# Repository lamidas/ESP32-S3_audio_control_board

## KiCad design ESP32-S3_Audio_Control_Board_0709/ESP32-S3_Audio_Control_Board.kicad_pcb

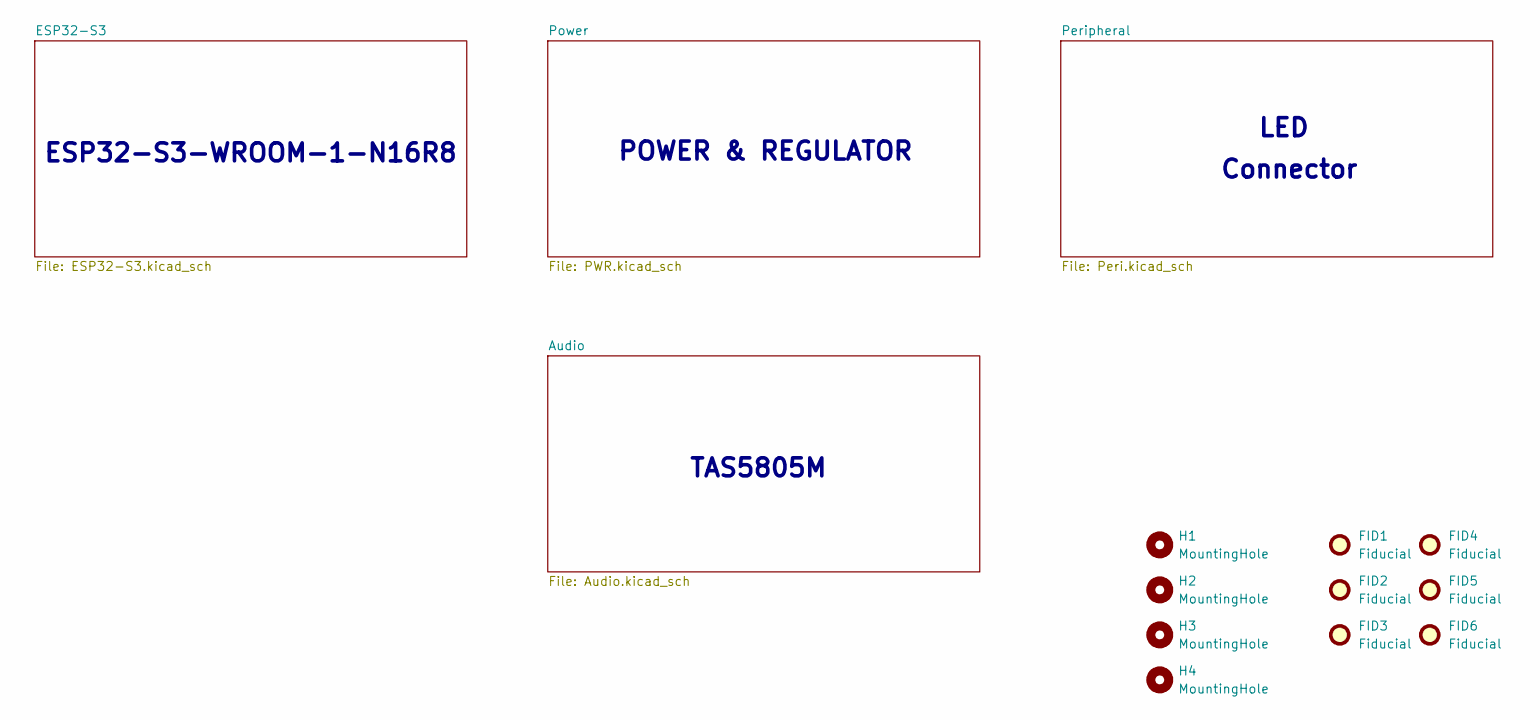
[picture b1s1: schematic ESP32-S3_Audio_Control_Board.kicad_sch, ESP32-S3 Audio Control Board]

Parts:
FID1, FID2, FID3, FID4, FID5, FID6: Fiducial; Fiducial_1mm_Mask2mm
H1, H2, H3, H4: MountingHole; MountingHole_3.5mm

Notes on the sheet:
ESP32-S3-WROOM-1-N16R8
Connector
TAS5805M
LED
POWER & REGULATOR

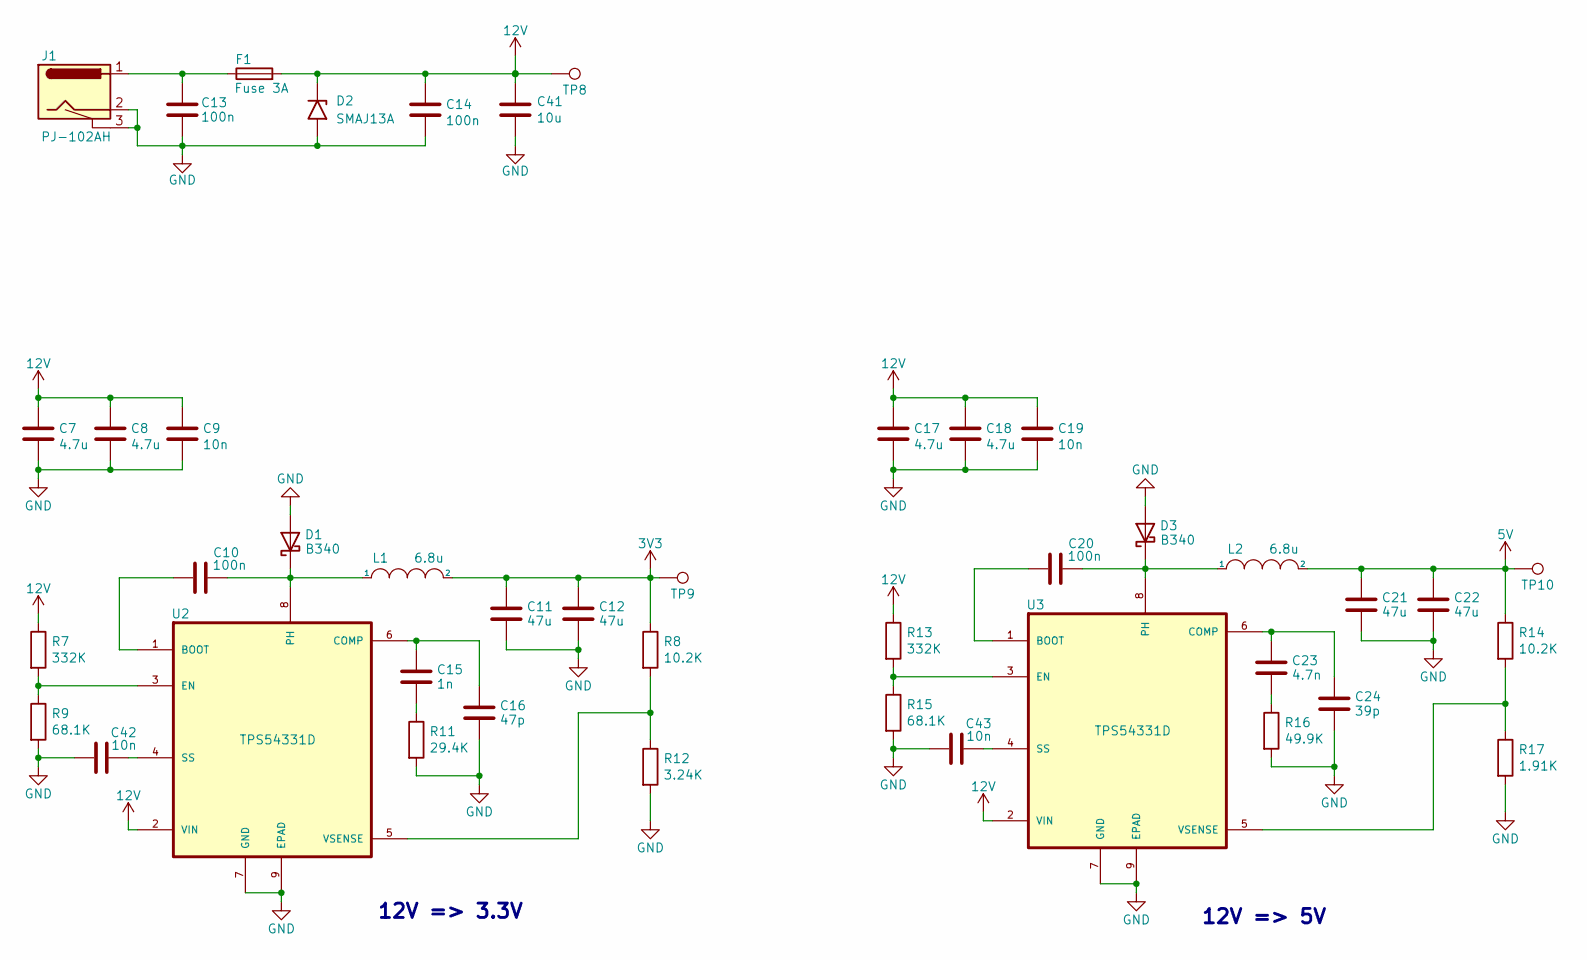
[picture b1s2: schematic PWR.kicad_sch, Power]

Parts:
C7, C8, C17, C18: 4.7u; C_0805_2012Metric; Mfr PN GRM21BZ7YA475KE15K
C9, C19, C42, C43: 10n; C_0402_1005Metric; Mfr PN CC0402KRX7R9BB103
C10, C14, C20: 100n; C_0402_1005Metric; Mfr PN GCM155R71H104KE02D
C11, C12, C21, C22: 47u; C_1210_3225Metric; Mfr PN GRM32ER61C476KE15L
C13: 100n; C_0402_1005Metric; Part Description CAP CER 100nF 50V X7R 0402
C15: 1n; C_0402_1005Metric; Mfr PN GRM155R71H102KA01D
C16: 47p; C_0402_1005Metric; Mfr PN GRM1555C1H470JA01D
C23: 4.7n; C_0402_1005Metric; Mfr PN CC0402KRX7R9BB472
C24: 39p; C_0402_1005Metric; Mfr PN CC0402JRNPO9BN390
C41: 10u; C_0805_2012Metric; Mfr PN GRM21BR6YA106KE43L
D1, D3: B340; D_SMA; Mfr PN B340A
D2: SMAJ13A; D_SMA; Mfr PN SMAJ13A
F1: Fuse 3A; R_1812_4532Metric; Mfr PN SMD1812P300SLR/24
J1: PJ-102AH; BarrelJack_CUI_PJ-102AH_Horizontal; Mfr PN PJ-102AH
L1, L2: 6.8u; L_Sunlord_MWSA0602S; Mfr PN FXL0630-6R8-M
R7, R13: 332K; R_0402_1005Metric; Mfr PN 0402WGF3323TCE
R8, R14: 10.2K; R_0402_1005Metric; Mfr PN RC0402FR-0710K2L
R9, R15: 68.1K; R_0402_1005Metric; Mfr PN 0402WGF6812TCE
R11: 29.4K; R_0402_1005Metric; Mfr PN AT0402DRD0729K4L
R12: 3.24K; R_0402_1005Metric; Mfr PN 0402WGF3241TCE
R16: 49.9K; R_0402_1005Metric; Mfr PN ERJ2RKF4992X
R17: 1.91K; R_0402_1005Metric; Mfr PN 0402WGF1911TCE
TP8, TP9, TP10: IO0; TestPoint_Pad_D1.5mm
U2, U3: TPS54331D; SOIC-8-1EP_3.9x4.9mm_P1.27mm_EP2.29x3mm; Mfr PN TPS54331DR

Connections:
3V3: C11.2, C12.2, L1.2, R8.1, TP9.1 (1_1); also elsewhere on the board
5V: C21.2, C22.2, L2.2, R14.1, TP10.1 (1_1); also elsewhere on the board
12V: C7.1, C8.1, C9.1, C14.1, C17.1, C18.1, C19.1, C41.1, D2.1 (A1), F1.2, R7.1, R13.1, TP8.1 (1_1), U2.2 (VIN), U3.2 (VIN); also elsewhere on the board
GND: C7.2, C8.2, C9.2, C11.1, C12.1, C13.2, C14.2, C16.1, C17.2, C18.2, C19.2, C21.1, C22.1, C24.1, C41.2, C42.1, C43.1, D1.2 (A), D2.2 (A2), D3.2 (A), J1.2, J1.3, R9.2, R11.2, R12.2, R15.2, R16.2, R17.2, U2.7 (GND), U2.9 (EPAD), U3.7 (GND), U3.9 (EPAD); also elsewhere on the board
unnamed: C13.1, F1.1, J1.1
unnamed: C15.1, R11.1
unnamed: C23.1, R16.1
unnamed: C10.2, D1.1 (K), L1.1, U2.8 (PH)
unnamed: C20.2, D3.1 (K), L2.1, U3.8 (PH)
unnamed: C10.1, U2.1 (BOOT)
unnamed: C15.2, C16.2, U2.6 (COMP)
unnamed: R7.2, R9.1, U2.3 (EN)
unnamed: C42.2, U2.4 (SS)
unnamed: R8.2, R12.1, U2.5 (VSENSE)
unnamed: C20.1, U3.1 (BOOT)
unnamed: C23.2, C24.2, U3.6 (COMP)
unnamed: R13.2, R15.1, U3.3 (EN)
unnamed: C43.2, U3.4 (SS)
unnamed: R14.2, R17.1, U3.5 (VSENSE)

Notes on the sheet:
12V => 3.3V
12V => 5V

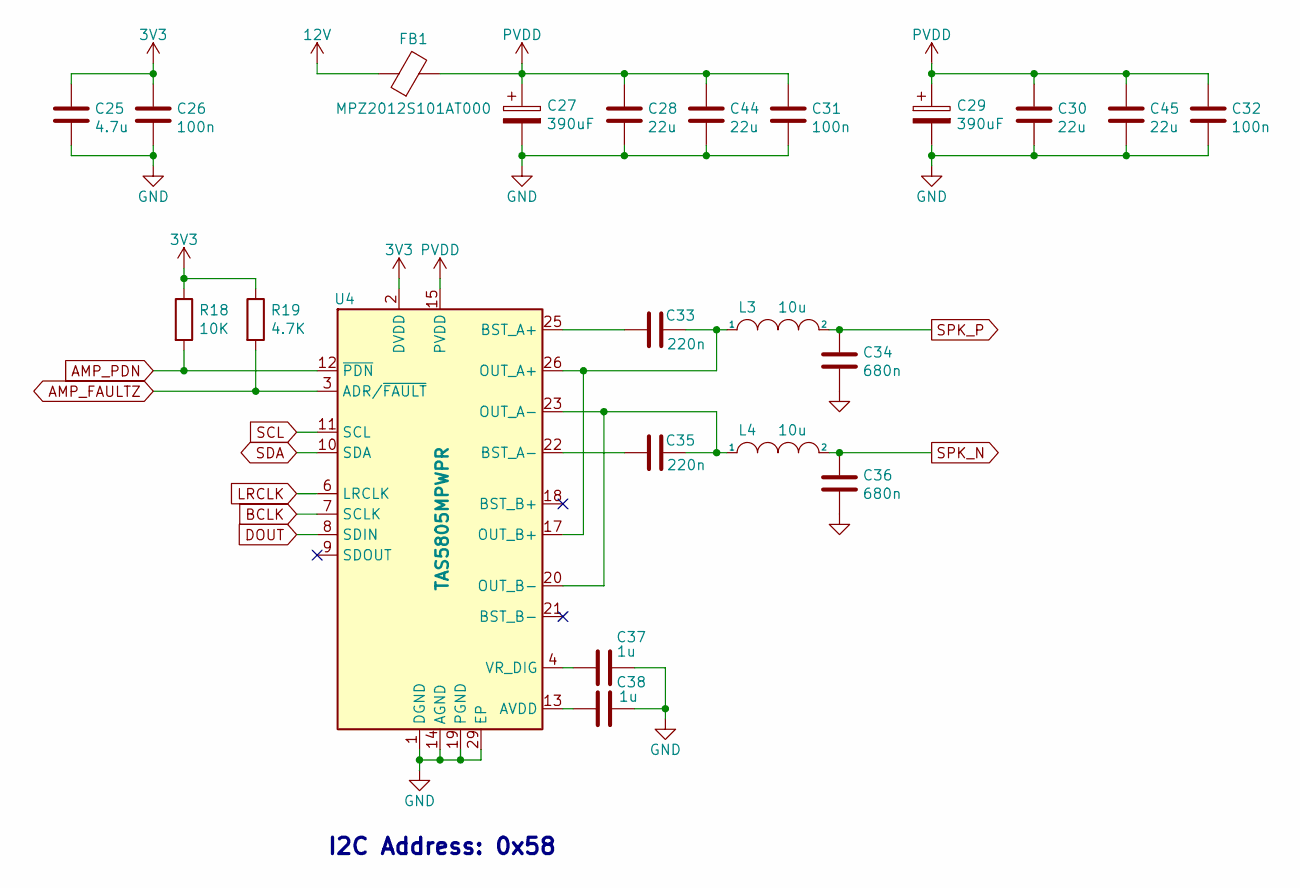
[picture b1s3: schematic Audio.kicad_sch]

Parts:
C25: 4.7u; C_0603_1608Metric; Mfr PN GRM188R61A475KE15D
C26: 100n; C_0402_1005Metric; Mfr PN GCM155R71H104KE02D
C27, C29: 390uF; CP_Elec_8x10.5; Mfr PN HV1E397M0810PZ
C28, C30, C44, C45: 22u; C_1206_3216Metric; Mfr PN GRM31CR61E226KE15L
C31, C32: 100n; C_0603_1608Metric; Mfr PN GCJ188R71E104KA12D
C33, C35: 220n; C_0603_1608Metric; Mfr PN GCM188R71H224KA64D
C34, C36: 680n; C_1206_3216Metric; Mfr PN CC1206KKX7R9BB684
C37, C38: 1u; C_0402_1005Metric; Mfr PN GRM155R61H105KE05D
FB1: MPZ2012S101AT000; Fuse_0805_2012Metric; Mfr PN MPZ2012S101AT000
L3, L4: 10u; L_KOHERelec_MDA7030; Mfr PN PSPMAA063T-100M-ANP
R18: 10K; R_0402_1005Metric; Mfr PN RC0402FR-0710KL
R19: 4.7K; R_0402_1005Metric; Mfr PN 0402WGF4701TCE
U4: TAS5805MPWPR; TSSOP-28-1EP_4.4x9.7mm_P0.65mm_EP3.4x9.7mm_Mask3.1x4.05mm_T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; Mfr PN TAS5805MPWPR

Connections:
3V3: C25.1, C26.1, R18.1, R19.1, U4.2 (DVDD); also elsewhere on the board
12V: FB1.1; also elsewhere on the board
AMP_FAULTZ: R19.2, U4.3 (ADR/~FAULT); also elsewhere on the board
AMP_PDN: R18.2, U4.12 (~PDN); also elsewhere on the board
BCLK: U4.7 (SCLK); also elsewhere on the board
DOUT: U4.8 (SDIN); also elsewhere on the board
GND: C25.2, C26.2, C27.2, C28.2, C29.2, C30.2, C31.2, C32.2, C34.1, C36.1, C37.2, C38.2, C44.2, C45.2, U4.1 (DGND), U4.5 (DGND), U4.14 (AGND), U4.19 (PGND), U4.24 (PGND), U4.29 (EP); also elsewhere on the board
LRCLK: U4.6 (LRCLK); also elsewhere on the board
unnamed: C38.1, U4.13 (AVDD)
unnamed: C33.1, U4.25 (BST_A+)
unnamed: C35.1, U4.22 (BST_A-)
unnamed: C33.2, L3.1, U4.17 (OUT_B+), U4.26 (OUT_A+)
unnamed: C35.2, L4.1, U4.20 (OUT_B-), U4.23 (OUT_A-)
unnamed: C37.1, U4.4 (VR_DIG)
PVDD: C27.1, C28.1, C29.1, C30.1, C31.1, C32.1, C44.1, C45.1, FB1.2, U4.15 (PVDD), U4.16 (PVDD), U4.27 (PVDD), U4.28 (PVDD)
SCL: U4.11 (SCL); also elsewhere on the board
SDA: U4.10 (SDA); also elsewhere on the board
SPK_N: C36.2, L4.2; also elsewhere on the board
SPK_P: C34.2, L3.2; also elsewhere on the board

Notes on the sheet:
I2C Address: 0x58

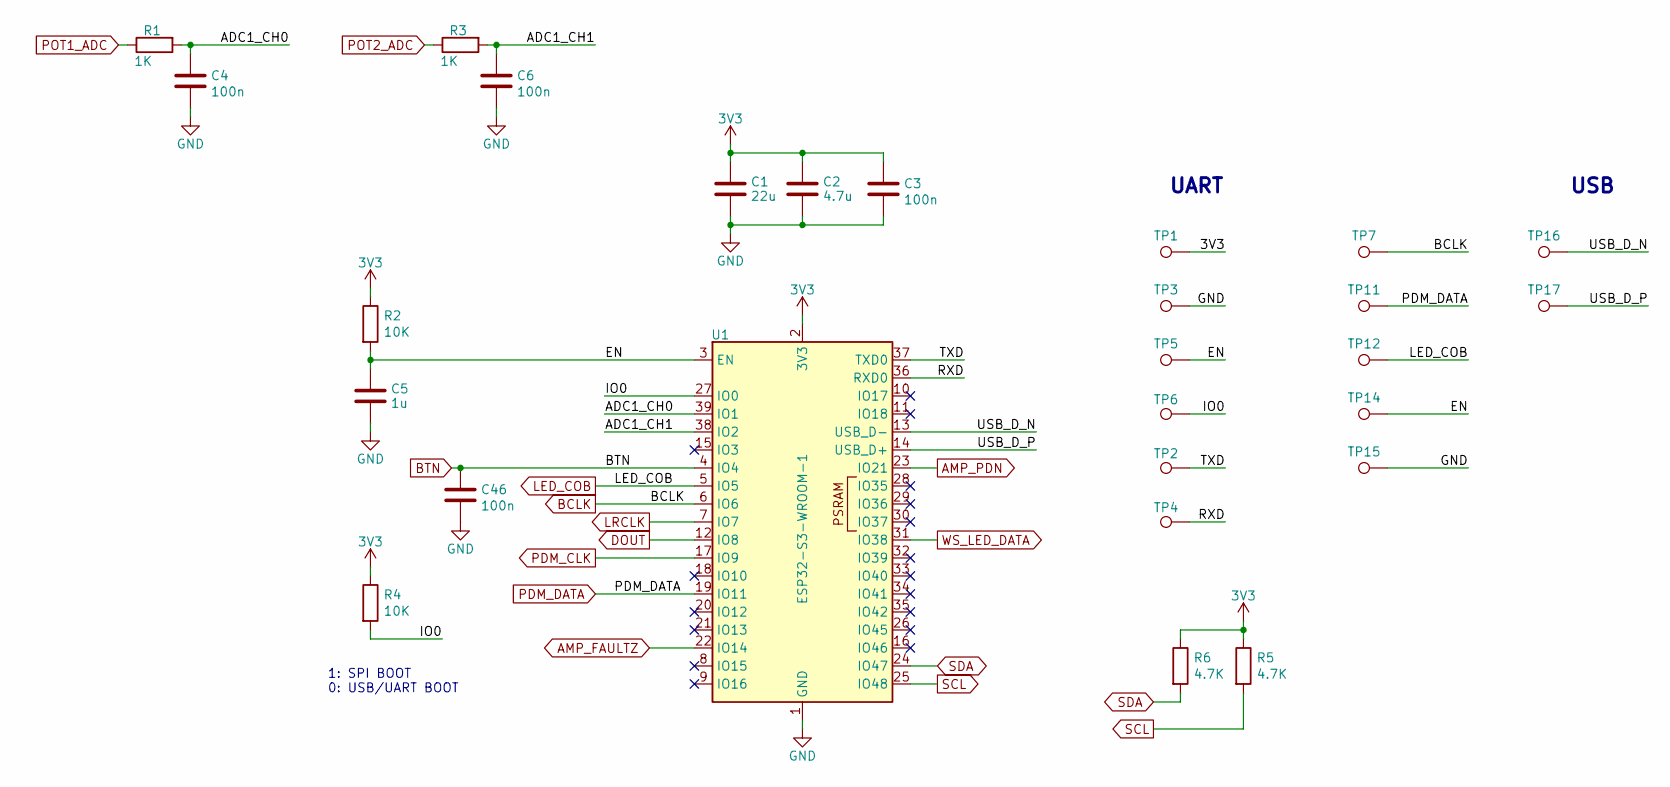
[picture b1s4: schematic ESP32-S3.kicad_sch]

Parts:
C1: 22u; C_0603_1608Metric; Mfr PN GRM188R61A226ME15D
C2: 4.7u; C_0402_1005Metric; Mfr PN GRM155R61A475KEAAD
C3, C4, C6, C46: 100n; C_0402_1005Metric; Mfr PN GCM155R71H104KE02D
C5: 1u; C_0402_1005Metric; Mfr PN GRM155R61H105KE05D
R1, R3: 1K; R_0402_1005Metric; Mfr PN 0402WGF1001TCE
R2, R4: 10K; R_0402_1005Metric; Mfr PN RC0402FR-0710KL
R5, R6: 4.7K; R_0402_1005Metric; Mfr PN 0402WGF4701TCE
TP1, TP2, TP3, TP4, TP5, TP6, TP7, TP11, TP12, TP14, TP15, TP16, TP17: IO0; TestPoint_Pad_D1.5mm
U1: ESP32-S3-WROOM-1; Mfr PN ESP32-S3-WROOM-1-N16R8

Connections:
3V3: C1.1, C2.1, C3.1, R2.1, R4.1, R5.1, R6.1, TP1.1 (1_1), U1.2 (3V3); also elsewhere on the board
/ESP32-S3/ADC1_CH0: C4.1, R1.2, U1.39 (IO1)
/ESP32-S3/ADC1_CH1: C6.1, R3.2, U1.38 (IO2)
/ESP32-S3/EN: C5.1, R2.2, TP5.1 (1_1), TP14.1 (1_1), U1.3 (EN)
/ESP32-S3/IO0: R4.2, TP6.1 (1_1), U1.27 (IO0)
/ESP32-S3/RXD: TP4.1 (1_1), U1.36 (RXD0)
/ESP32-S3/TXD: TP2.1 (1_1), U1.37 (TXD0)
/ESP32-S3/USB_D_N: TP16.1 (1_1), U1.13 (USB_D-)
/ESP32-S3/USB_D_P: TP17.1 (1_1), U1.14 (USB_D+)
AMP_FAULTZ: U1.22 (IO14); also elsewhere on the board
AMP_PDN: U1.23 (IO21); also elsewhere on the board
BCLK: TP7.1 (1_1), U1.6 (IO6); also elsewhere on the board
BTN: C46.1, U1.4 (IO4); also elsewhere on the board
DOUT: U1.12 (IO8); also elsewhere on the board
GND: C1.2, C2.2, C3.2, C4.2, C5.2, C6.2, C46.2, TP3.1 (1_1), TP15.1 (1_1), U1.1 (GND), U1.40 (GND), U1.41 (GND); also elsewhere on the board
LED_COB: TP12.1 (1_1), U1.5 (IO5); also elsewhere on the board
LRCLK: U1.7 (IO7); also elsewhere on the board
PDM_CLK: U1.17 (IO9); also elsewhere on the board
PDM_DATA: TP11.1 (1_1), U1.19 (IO11); also elsewhere on the board
POT1_ADC: R1.1; also elsewhere on the board
POT2_ADC: R3.1; also elsewhere on the board
SCL: R5.2, U1.25 (IO48); also elsewhere on the board
SDA: R6.2, U1.24 (IO47); also elsewhere on the board
WS_LED_DATA: U1.31 (IO38); also elsewhere on the board

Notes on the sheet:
UART
1: SPI BOOT 0: USB/UART BOOT
USB

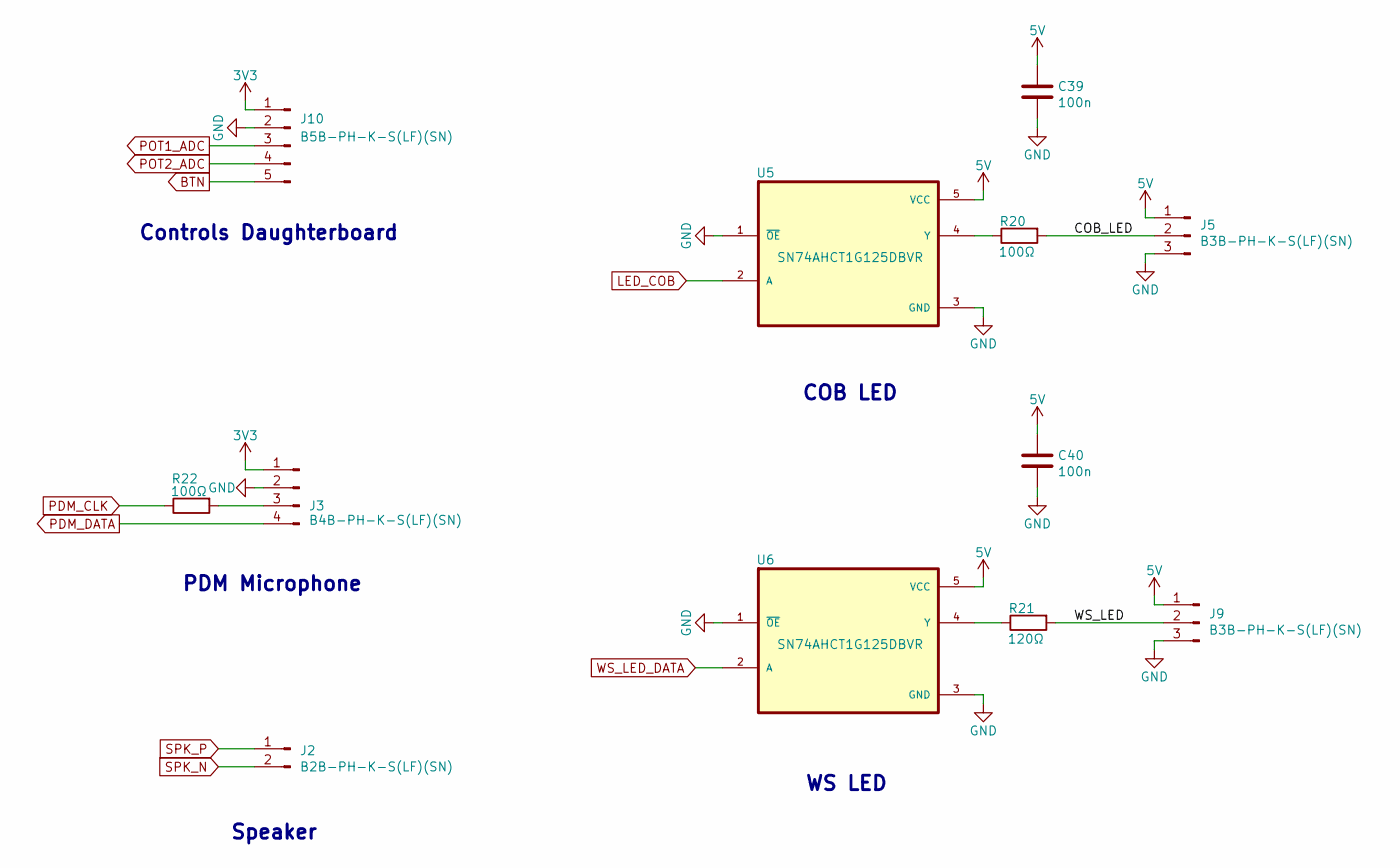
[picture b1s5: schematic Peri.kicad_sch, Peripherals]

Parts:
C39, C40: 100n; C_0402_1005Metric; Mfr PN GCM155R71H104KE02D
J2: B2B-PH-K-S(LF)(SN); JST_PH_B2B-PH-K_1x02_P2.00mm_Vertical; Mfr PN B2B-PH-K-S(LF)(SN)
J3: B4B-PH-K-S(LF)(SN); JST_PH_B4B-PH-K_1x04_P2.00mm_Vertical; Mfr PN B4B-PH-K-S(LF)(SN)
J5, J9: B3B-PH-K-S(LF)(SN); JST_PH_B3B-PH-K_1x03_P2.00mm_Vertical; Mfr PN B3B-PH-K-S(LF)(SN)
J10: B5B-PH-K-S(LF)(SN); JST_PH_B5B-PH-K_1x05_P2.00mm_Vertical; Mfr PN B5B-PH-K-S(LF)(SN)
R20, R22: 100Ω; R_0402_1005Metric; Mfr PN 0402WGF1000TCE
R21: 120Ω; R_0402_1005Metric; Mfr PN ERJ2RKF1200X
U5, U6: SN74AHCT1G125DBVR; SOT-23-5; Mfr PN SN74AHCT1G125DBVR

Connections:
3V3: J3.1, J10.1; also elsewhere on the board
5V: C39.1, C40.1, J5.1, J9.1, U5.5 (VCC), U6.5 (VCC); also elsewhere on the board
/Peripheral/COB_LED: J5.2, R20.2
/Peripheral/WS_LED: J9.2, R21.2
BTN: J10.5; also elsewhere on the board
GND: C39.2, C40.2, J3.2, J5.3, J9.3, J10.2, U5.1 (~OE), U5.3 (GND), U6.1 (~OE), U6.3 (GND); also elsewhere on the board
LED_COB: U5.2 (A); also elsewhere on the board
unnamed: J3.3, R22.2
unnamed: R20.1, U5.4 (Y)
unnamed: R21.1, U6.4 (Y)
PDM_CLK: R22.1; also elsewhere on the board
PDM_DATA: J3.4; also elsewhere on the board
POT1_ADC: J10.3; also elsewhere on the board
POT2_ADC: J10.4; also elsewhere on the board
SPK_N: J2.2; also elsewhere on the board
SPK_P: J2.1; also elsewhere on the board
WS_LED_DATA: U6.2 (A); also elsewhere on the board

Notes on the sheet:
Speaker
WS LED
COB LED
PDM Microphone
Controls Daughterboard

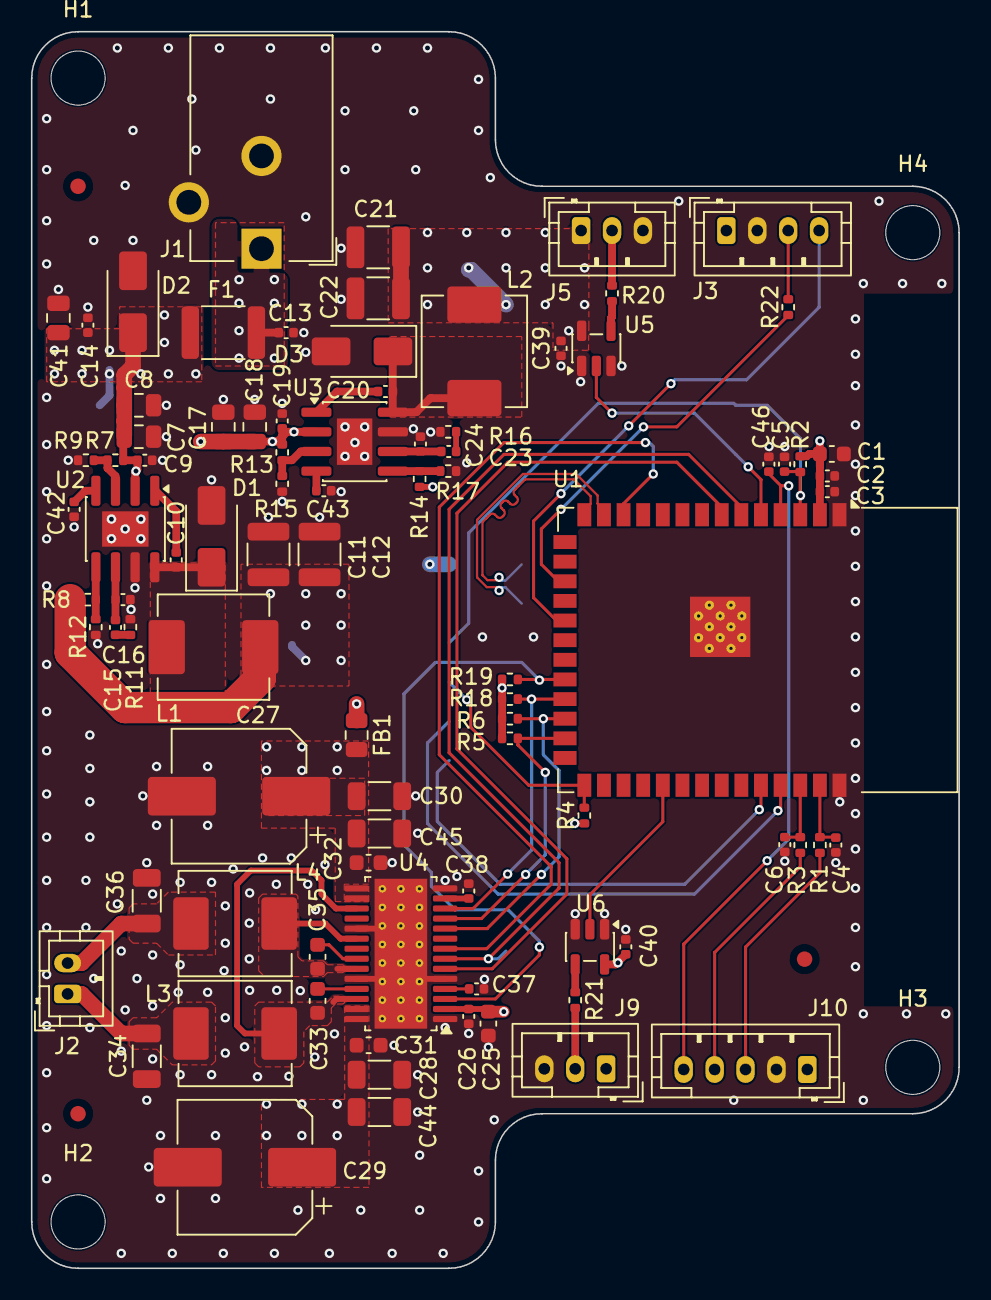
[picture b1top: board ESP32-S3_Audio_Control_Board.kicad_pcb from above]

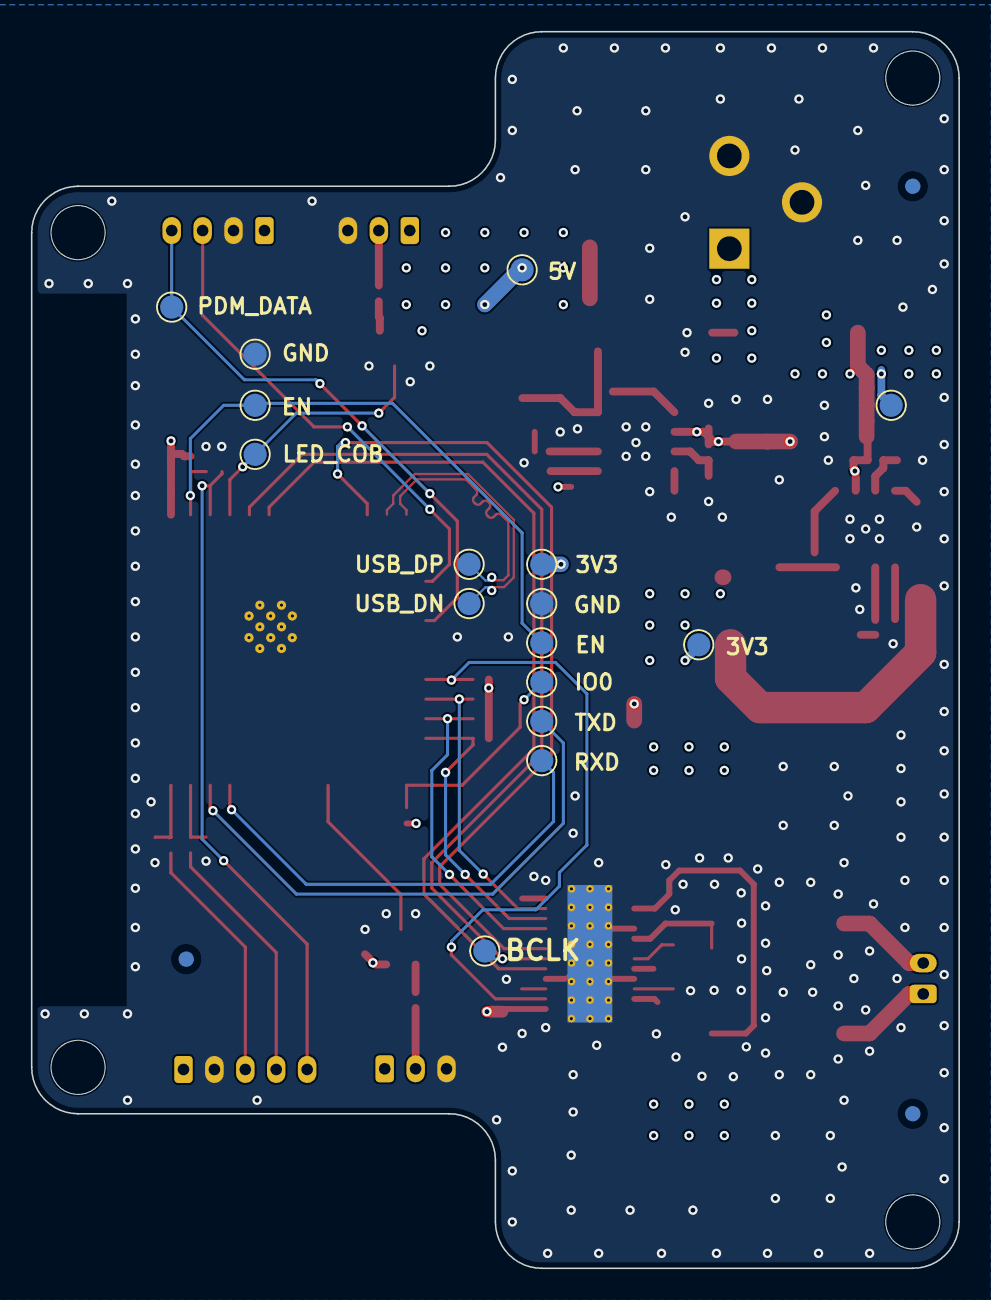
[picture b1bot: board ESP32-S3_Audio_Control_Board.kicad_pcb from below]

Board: 4 copper layers, 60.0 x 80.0 mm, 114 parts (19 on the bottom side), 55 nets.

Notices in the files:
parts and their libraries:
License: Apache-2.0
